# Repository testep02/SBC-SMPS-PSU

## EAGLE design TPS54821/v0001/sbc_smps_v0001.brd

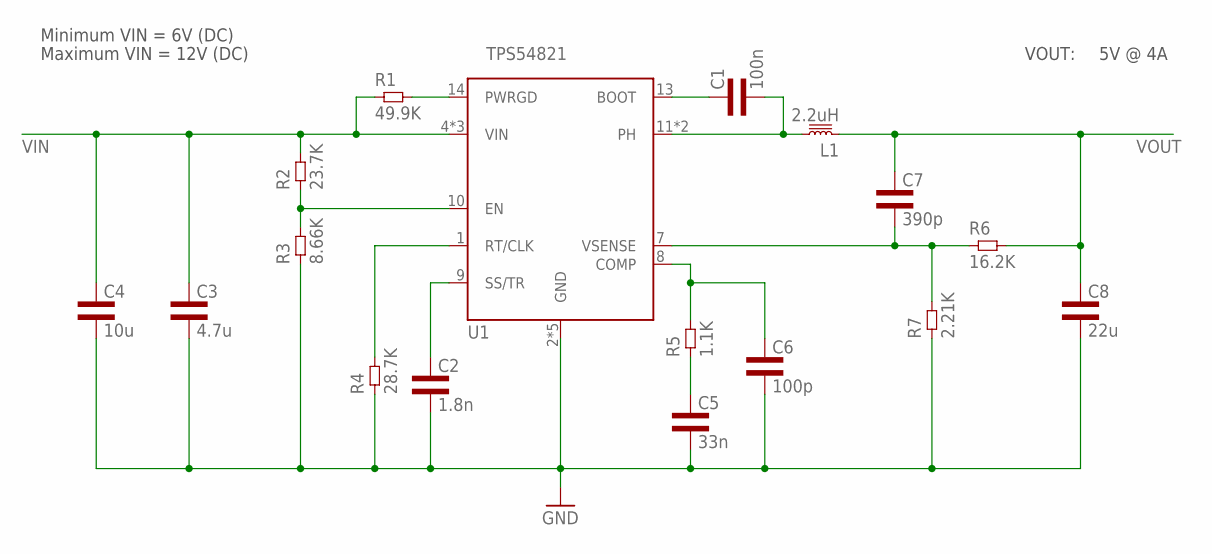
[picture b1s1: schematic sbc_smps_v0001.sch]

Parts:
C1: 100n; 0603L3
C2: 1.8n; 0402L3
C3: 4.7u; 0805L3
C4: 10u; 1206L3
C5: 33n; 0402L3
C6: 100p; 0402L3
C7: 390p; 0402L3
C8: 22u; 1206L3
L1: 2.2uH; 5.7X5.2
R1: 49.9K; 0402L3
R2: 23.7K; 0402L3
R3: 8.66K; 0402L3
R4: 28.7K; 0402L3
R5: 1.1K; 0402L3
R6: 16.2K; 0402L3
R7: 2.21K; 0402L3
U1: TPS54821; VQFN-14

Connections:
GND: C2.P$2 (2), C3.2, C4.2, C5.P$2 (2), C6.P$2 (2), C8.2, R3.P$1 (1), R4.P$1 (1), R7.P$1 (1), U1.2 (GND), U1.3 (GND), U1.TP@1 (GND), U1.TP@2 (GND), U1.TP@3 (GND)
unnamed: C1.P$1 (1), U1.13 (BOOT)
unnamed: C1.P$2 (2), L1.2, U1.11 (PH), U1.12 (PH)
unnamed: R1.P$2 (2), U1.14 (PWRGD)
unnamed: R2.P$1 (1), R3.P$2 (2), U1.10 (EN)
unnamed: C2.P$1 (1), U1.9 (SS/TR)
unnamed: R4.P$2 (2), U1.1 (RT/CLK)
unnamed: C6.P$1 (1), R5.P$2 (2), U1.8 (COMP)
unnamed: C5.P$1 (1), R5.P$1 (1)
unnamed: C7.P$2 (2), R6.P$1 (1), R7.P$2 (2), U1.7 (VSENSE)
VIN: C3.1, C4.1, R1.P$1 (1), R2.P$2 (2), U1.4 (VIN), U1.5 (VIN), U1.6 (VIN)
VOUT: C7.P$1 (1), C8.1, L1.1, R6.P$2 (2)

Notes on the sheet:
Minimum VIN = 6V (DC)
Maximum VIN = 12V (DC)
VOUT:
5V @ 4A

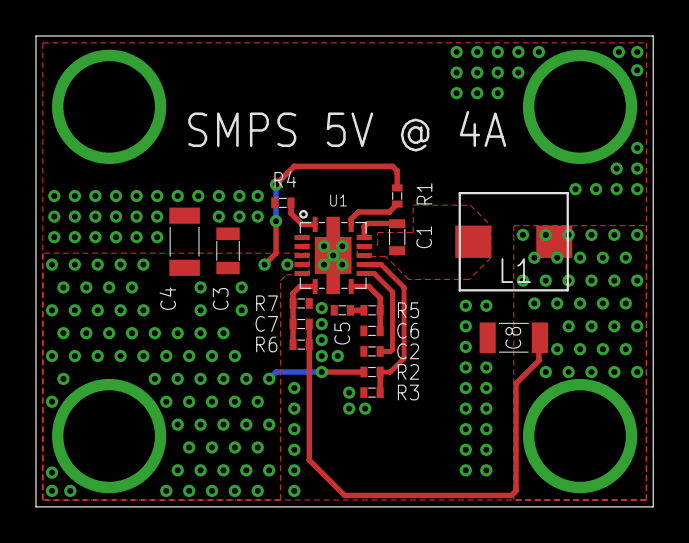
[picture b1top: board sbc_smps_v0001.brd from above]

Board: 2 copper layers, 34.3 x 26.2 mm, 17 parts (0 on the bottom side), 12 nets.

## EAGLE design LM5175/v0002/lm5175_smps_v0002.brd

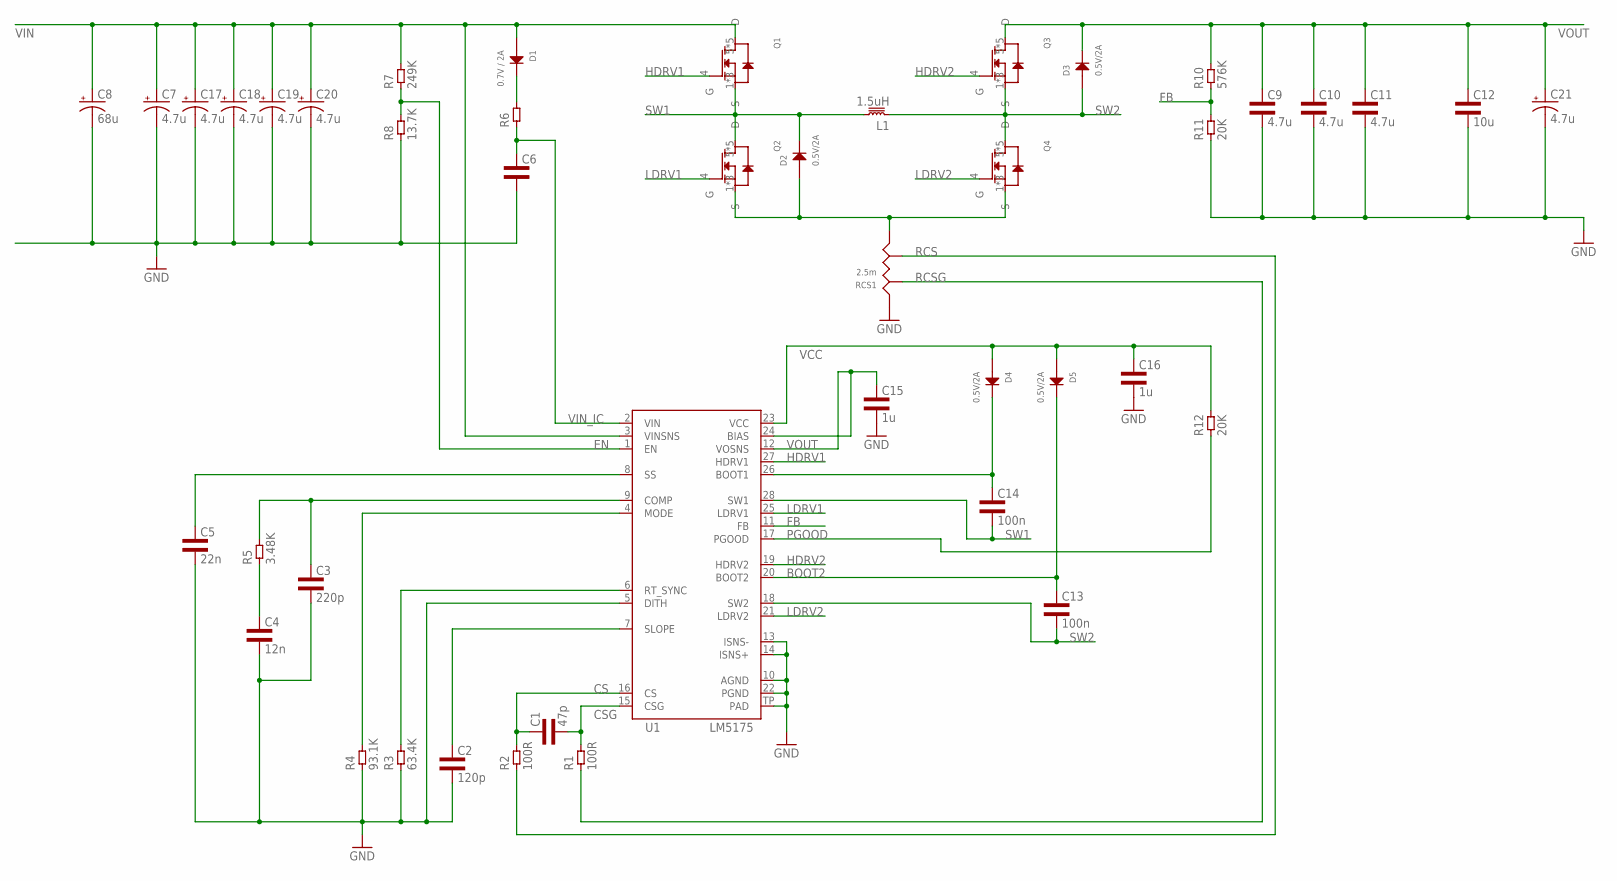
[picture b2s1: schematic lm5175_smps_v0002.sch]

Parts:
C1: 47p; 0402L3
C2: 120p; 0603L3
C3: 220p; 0603L3
C4: 12n; 0603L3
C5: 22n; 0603L3
C6: CAP0603L3; 0603L3
C7, C17, C18, C19, C20, C21: 4.7u; SANYO-OSCON_SMD_E12
C8: 68u; 153CLV-0810
C9, C10, C11: 4.7u; 1206L3
C12: 10u; 1206L3
C13, C14: 100n; 0603L3
C15, C16: 1u; 0603L3
D1: 0.7V / 2A; SMA-2
D2, D3, D4, D5: 0.5V/2A; SMA-2
L1: 1.5uH; 5.7X5.2
Q1, Q2, Q3, Q4: CSD18540Q5B; Q5B
R1, R2: 100R; 0603L3
R3: 63.4K; 0603L3
R4: 93.1K; 0603L3
R5: 3.48K; 0603L3
R6: RES0603L3; 0603L3
R7: 249K; 0603L3
R8: 13.7K; 0603L3
R10: 576K; 0603L3
R11, R12: 20K; 0603L3
RCS1: 2.5m; R2512
U1: LM5175; R-PDSO-G28

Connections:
BOOT2: C13.P$1 (1), D5.2 (CATHODE), U1.20 (BOOT2)
CS: C1.P$1 (1), R2.P$2 (2), U1.16 (CS)
CSG: C1.P$2 (2), R1.P$2 (2), U1.15 (CSG)
EN: R7.P$1 (1), R8.P$2 (2), U1.1 (EN)
FB: R10.P$1 (1), R11.P$2 (2), U1.11 (FB)
GND: C2.P$2 (2), C3.P$2 (2), C4.P$2 (2), C5.P$2 (2), C6.P$2 (2), C7.-, C8.-, C9.2, C10.2, C11.2, C12.2, C15.P$2 (2), C16.P$2 (2), C17.-, C18.-, C19.-, C20.-, C21.-, R3.P$1 (1), R4.P$1 (1), R8.P$1 (1), R11.P$1 (1), RCS1.1_1 (1), RCS1.1_2 (1), U1.5 (DITH), U1.10 (AGND), U1.13 (ISNS-), U1.14 (ISNS+), U1.22 (PGND), U1.TP (PAD)
HDRV1: Q1.4 (G), U1.27 (HDRV1)
HDRV2: Q3.4 (G), U1.19 (HDRV2)
LDRV1: Q2.4 (G), U1.25 (LDRV1)
LDRV2: Q4.4 (G), U1.21 (LDRV2)
unnamed: C2.P$1 (1), U1.7 (SLOPE)
unnamed: R3.P$2 (2), U1.6 (RT_SYNC)
unnamed: R4.P$2 (2), U1.4 (MODE)
unnamed: C4.P$1 (1), R5.P$1 (1)
unnamed: C3.P$1 (1), R5.P$2 (2), U1.9 (COMP)
unnamed: C5.P$1 (1), U1.8 (SS)
unnamed: D1.2 (CATHODE), R6.P$2 (2)
unnamed: C14.P$1 (1), D4.2 (CATHODE), U1.26 (BOOT1)
PGOOD: R12.P$1 (1), U1.17 (PGOOD)
RCS: R2.P$1 (1), RCS1.CS_2
RCSG: R1.P$1 (1), RCS1.CS_1
SNS_HIGH: D2.1 (ANODE), Q2.1 (S), Q2.2 (S), Q2.3 (S), Q4.1 (S), Q4.2 (S), Q4.3 (S), RCS1.2_1 (2), RCS1.2_2 (2)
SW1: C14.P$2 (2), D2.2 (CATHODE), L1.2, Q1.1 (S), Q1.2 (S), Q1.3 (S), Q2.5 (D), Q2.6 (D), Q2.7 (D), Q2.8 (D), Q2.9 (D), U1.28 (SW1)
SW2: C13.P$2 (2), D3.1 (ANODE), L1.1, Q3.1 (S), Q3.2 (S), Q3.3 (S), Q4.5 (D), Q4.6 (D), Q4.7 (D), Q4.8 (D), Q4.9 (D), U1.18 (SW2)
VCC: C16.P$1 (1), D4.1 (ANODE), D5.1 (ANODE), R12.P$2 (2), U1.23 (VCC)
VIN: C7.+, C8.+, C17.+, C18.+, C19.+, C20.+, D1.1 (ANODE), Q1.5 (D), Q1.6 (D), Q1.7 (D), Q1.8 (D), Q1.9 (D), R7.P$2 (2), U1.3 (VINSNS)
VIN_IC: C6.P$1 (1), R6.P$1 (1), U1.2 (VIN)
VOUT: C9.1, C10.1, C11.1, C12.1, C15.P$1 (1), C21.+, D3.2 (CATHODE), Q3.5 (D), Q3.6 (D), Q3.7 (D), Q3.8 (D), Q3.9 (D), R10.P$2 (2), U1.12 (VOSNS), U1.24 (BIAS)

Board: 2 copper layers, 44 parts (1 on the bottom side), 28 nets, no tracks yet.

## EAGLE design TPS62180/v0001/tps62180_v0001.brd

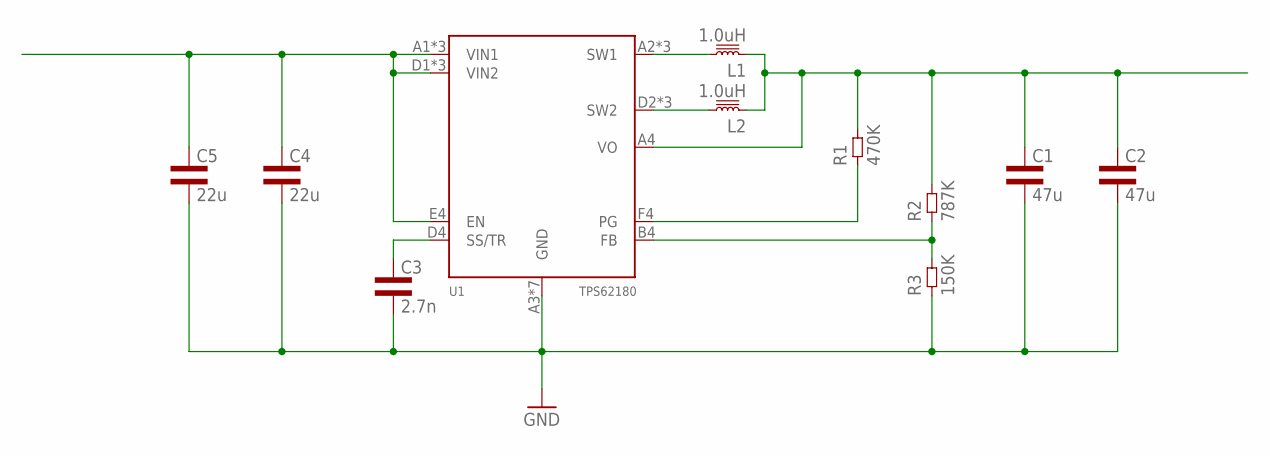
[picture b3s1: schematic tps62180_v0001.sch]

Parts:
C1, C2: 47u; 1206L3
C3: 2.7n; 0402L3
C4, C5: 22u; 1206L3
L1, L2: 1.0uH; SPM3012
R1: 470K; 0603L3
R2: 787K; 0603L3
R3: 150K; 0603L3
U1: TPS62180; R-XBGA-N24

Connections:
FB: R2.P$1 (1), R3.P$2 (2), U1.B4 (FB)
GND: C1.2, C2.2, C3.P$2 (2), C4.2, C5.2, R3.P$1 (1), U1.A3 (GND), U1.B3 (GND), U1.C3 (GND), U1.C4 (GND), U1.D3 (GND), U1.E3 (GND), U1.F3 (GND)
PG: R1.P$1 (1), U1.F4 (PG)
SS: C3.P$1 (1), U1.D4 (SS/TR)
SW1: L1.2, U1.A2 (SW1), U1.B2 (SW1), U1.C2 (SW1)
SW2: L2.2, U1.D2 (SW2), U1.E2 (SW2), U1.F2 (SW2)
VIN: C4.1, C5.1, U1.A1 (VIN1), U1.B1 (VIN1), U1.C1 (VIN1), U1.D1 (VIN2), U1.E1 (VIN2), U1.E4 (EN), U1.F1 (VIN2)
VOUT: C1.1, C2.1, L1.1, L2.1, R1.P$2 (2), R2.P$2 (2), U1.A4 (VO)

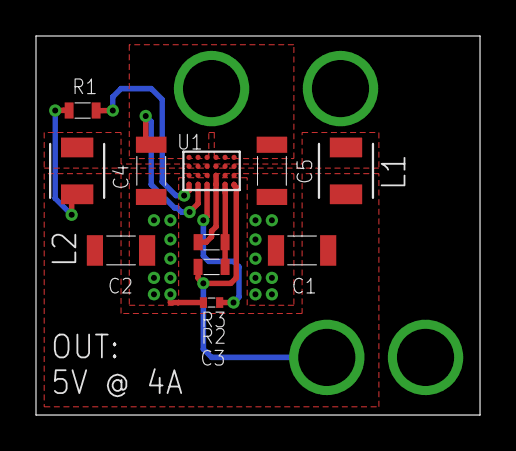
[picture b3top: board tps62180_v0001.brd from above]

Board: 2 copper layers, 24.7 x 21.1 mm, 11 parts (0 on the bottom side), 8 nets.

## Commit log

2017-03-01 Initial commit of single-board computer PSUs

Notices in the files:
parts and their libraries:
SparkFun-Aesthetics: Licensing: CC v3.0 Share-Alike You are welcome to use this library for commercial purposes.
